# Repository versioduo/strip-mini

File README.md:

# strip-mini
🚦 LED strip hardware

## Board

## Video
[YouTube](https://www.youtube.com/watch?v=P1gKQrn-1O4)

## Schematic

[PDF](strip-mini.pdf)

## Bill Of Materials

[Interactive BOM](https://htmlpreview.github.io/?https://github.com/versioduo/strip-mini/main/strip-mini-bom.html)

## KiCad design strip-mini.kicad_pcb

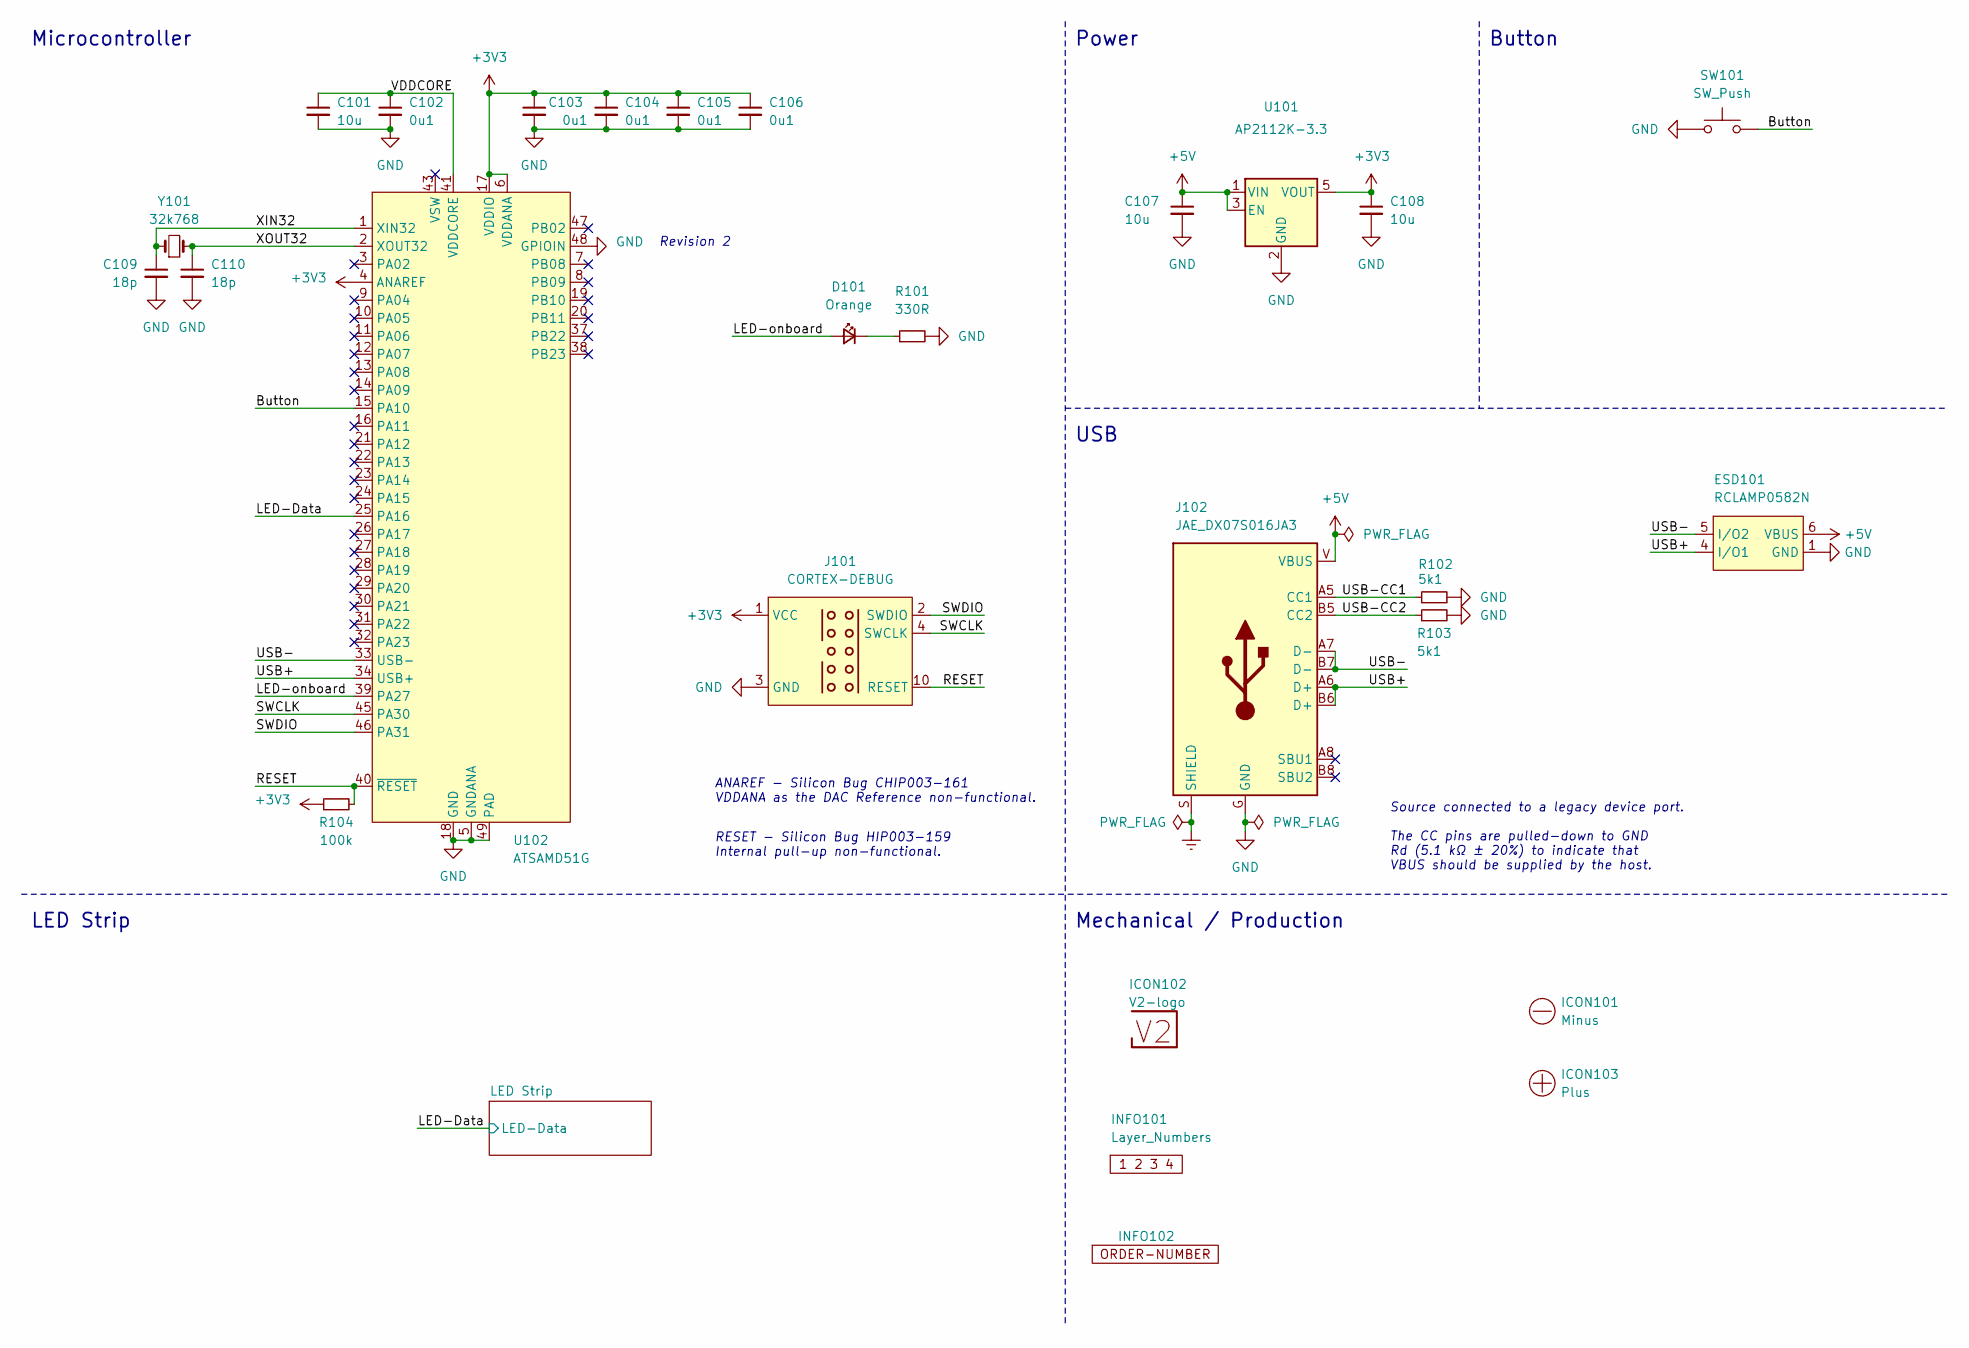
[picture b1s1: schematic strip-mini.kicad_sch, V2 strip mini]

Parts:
C101, C107, C108: 10u; C_0603_1608Metric
C102, C103, C104, C105, C106: 0u1; C_0603_1608Metric
C109, C110: 18p; C_0603_1608Metric
D101: Orange; LED_0603_1608Metric
ESD101: RCLAMP0582N; SLP1210N6
ICON101: Minus; Minus_Small
ICON102: V2-logo; Logo_Tiny
ICON103: Plus; Plus_Small
INFO101: Layer_Numbers
INFO102: ORDER-NUMBER; Order_Number
J101: CORTEX-DEBUG; Cortex_Debug_Pad
J102: JAE_DX07S016JA3
R101: 330R; R_0603_1608Metric
R102, R103: 5k1; R_0603_1608Metric
R104: 100k; R_0603_1608Metric
SW101: SW_Push; SKSG
U101: AP2112K-3.3; SOT-23-5
U102: ATSAMD51G; QFN-48-1EP_7x7mm_P0.5mm_EP5.45x5.45mm_ThermalVias
Y101: 32k768; Crystal_SMD_3215-2Pin_3.2x1.5mm

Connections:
+3V3: C103.1, C104.1, C105.1, C106.1, C108.1, J101.1 (VCC), R104.1, U101.5 (VOUT), U102.4 (ANAREF), U102.6 (VDDANA), U102.17 (VDDIO), U102.36 (VDDIO), U102.44 (VDDIO)
+5V: C107.1, ESD101.6 (VBUS), J102.V (VBUS), U101.1 (VIN), U101.3 (EN); also elsewhere on the board
/Button: SW101.2, U102.15 (PA10)
/LED-Data: U102.25 (PA16); also elsewhere on the board
/LED-onboard: D101.2 (A), U102.39 (PA27)
/RESET: J101.10 (RESET), R104.2, U102.40 (~RESET)
/SWCLK: J101.4 (SWCLK), U102.45 (PA30)
/SWDIO: J101.2 (SWDIO), U102.46 (PA31)
/USB+: ESD101.4 (I/O1), J102.A6 (D+), J102.B6 (D+), U102.34 (USB+)
/USB-: ESD101.5 (I/O2), J102.A7 (D-), J102.B7 (D-), U102.33 (USB-)
/USB-CC1: J102.A5 (CC1), R102.1
/USB-CC2: J102.B5 (CC2), R103.1
/VDDCORE: C101.1, C102.1, U102.41 (VDDCORE)
/XIN32: C109.1, U102.1 (XIN32), Y101.1
/XOUT32: C110.1, U102.2 (XOUT32), Y101.2
Earth: J102.S (SHIELD)
GND: C101.2, C102.2, C103.2, C104.2, C105.2, C106.2, C107.2, C108.2, C109.2, C110.2, ESD101.1 (GND), J101.3 (GND), J101.5 (GND), J102.G (GND), R101.2, R102.2, R103.2, SW101.1, U101.2 (GND), U102.5 (GNDANA), U102.18 (GND), U102.35 (GND), U102.42 (GND), U102.48 (GPIOIN), U102.49 (PAD); also elsewhere on the board
unnamed: D101.1 (K), R101.1

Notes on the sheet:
ANAREF - ﻿Silicon Bug CHIP003-161 VDDANA as the DAC Reference non-functional.
RESET - ﻿Silicon Bug HIP003-159 Internal pull-up non-functional.
﻿Source connected to a legacy device port. The CC pins are pulled-down to GND Rd (5.1 kΩ ± 20%) to indicate that VBUS should be supplied by the host.
Button
Revision 2
Power
Mechanical / Production
Microcontroller
USB
LED Strip

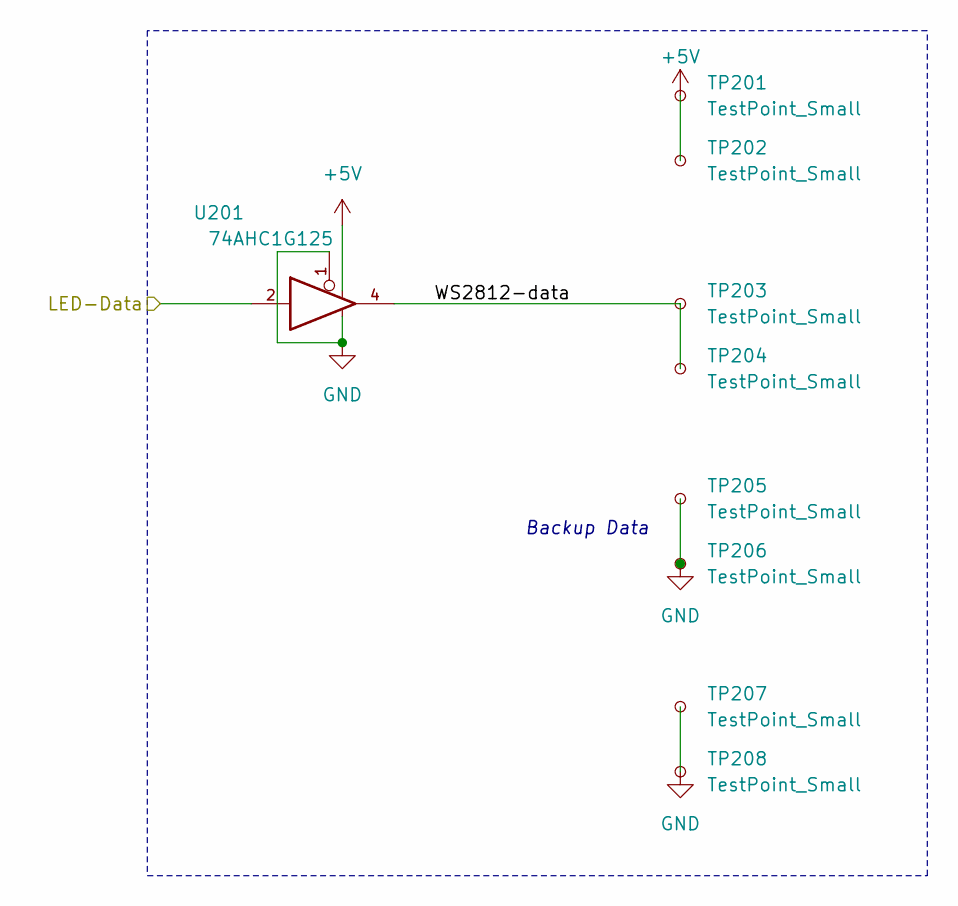
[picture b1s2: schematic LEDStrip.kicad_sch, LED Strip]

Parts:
TP201, TP202, TP203, TP204, TP205, TP206, TP207, TP208: TestPoint_Small; TestPoint_Pad_2.0x2.0mm
U201: 74AHC1G125; SOT-23-5

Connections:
+5V: TP201.1, TP202.1, U201.5; also elsewhere on the board
/LED Strip/WS2812-data: TP203.1, TP204.1, U201.4
/LED-Data: U201.2; also elsewhere on the board
GND: TP205.1, TP206.1, TP207.1, TP208.1, U201.1, U201.3; also elsewhere on the board

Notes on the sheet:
Backup Data

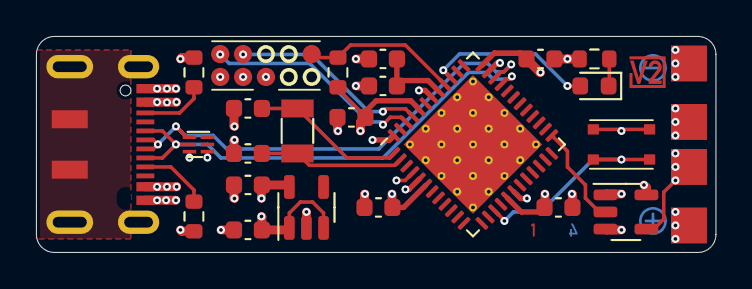
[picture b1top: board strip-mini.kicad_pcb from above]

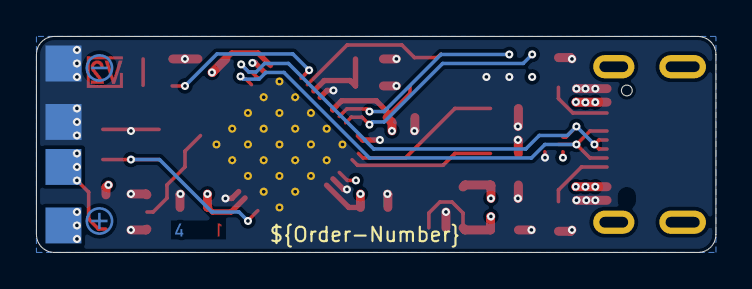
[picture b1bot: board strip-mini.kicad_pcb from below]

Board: 4 copper layers, 37.8 x 12.0 mm, 36 parts (7 on the bottom side), 18 nets.

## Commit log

2023-06-09 Import
2023-07-16 Refresh
2024-03-28 Update to Kicad 8
